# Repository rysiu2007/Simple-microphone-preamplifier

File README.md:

# Dual-Channel Microphone Preamplifier (F4558)

This repository contains the design and documentation for a high-gain microphone preamplifier utilizing the **F4558 Dual Operational Amplifier**. The circuit is optimized for low-noise amplification of small-signal audio inputs.

## ⚡ Circuit Features
*   **Topology:** Inverting Transimpedance Amplifier (TIA) configuration.
*   **Constant Gain:** Fixed by a **470kΩ** precision feedback resistor.
*   **Stability:** Includes a **10pF** compensation capacitor ($C_6/C_7$) in parallel with the feedback loop to prevent high-frequency oscillation and roll off ultrasonic noise.
*   **Biasing:** Virtual ground established at **+6V** (half-supply) to allow for single-supply operation from a +12V source.
*   **Input Stage:** AC-coupled via **4.7µF** electrolytic capacitors with 10kΩ pull-ups for microphone biasing.

## 🖼 Schematic Overview
The design uses both halves of the F4558 (U1A and U1B) to provide dual-channel processing. 

## 📂 Project Files
*   **[mic-amp-report.pdf](mic-amp-report.pdf)**: Full engineering report, including frequency response curves and BOM.
*   **index.html**: Project landing page.

## 🚀 Calculations
The gain for this specific inverting setup is defined by the input impedance of the microphone vs the feedback resistor ($R_f$):

$$V_{out} \approx -I_{in} \times R_f$$

The low-pass cutoff frequency ($f_c$) created by the feedback network is:
$$f_c = \frac{1}{2\pi \times 470k\Omega \times 10pF} \approx 33.8 \text{ kHz}$$
This ensures the full audible spectrum is captured while filtering out unwanted RF interference.

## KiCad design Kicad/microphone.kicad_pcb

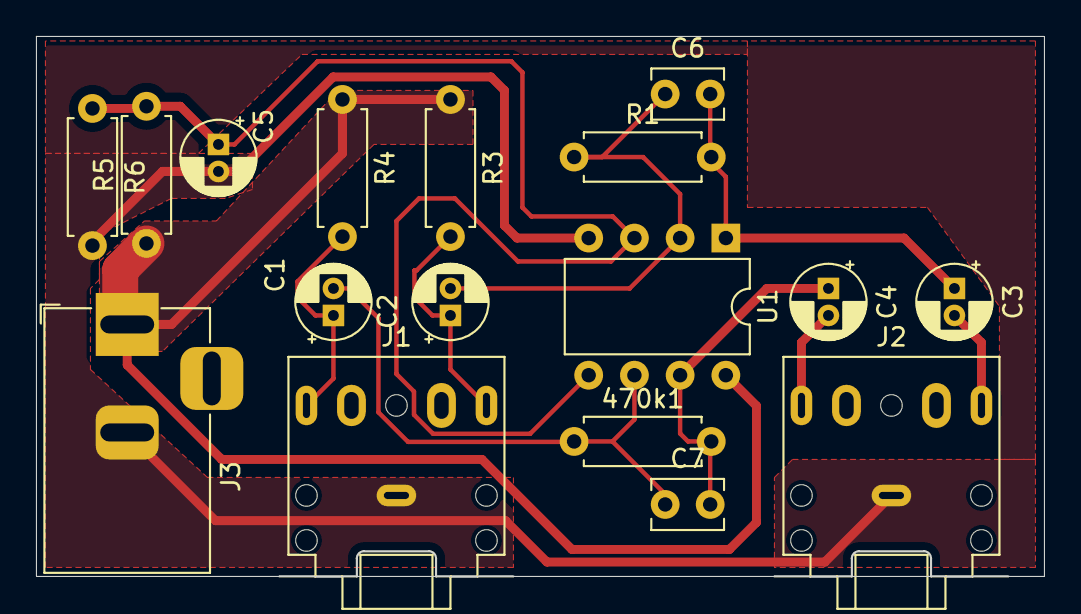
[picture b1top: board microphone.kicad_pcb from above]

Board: 2 copper layers, 56.0 x 30.0 mm, 17 parts (0 on the bottom side), 11 nets.

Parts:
470k1: R; R_Axial_DIN0207_L6.3mm_D2.5mm_P7.62mm_Horizontal
C1, C2, C3, C4, C5: 4.7u; CP_Radial_D4.0mm_P1.50mm
C6, C7: 10p; C_Disc_D3.8mm_W2.6mm_P2.50mm
J1: IN; Jack_3.5mm_CUI_SJ1-3525N_Horizontal
J2: OUT; Jack_3.5mm_CUI_SJ1-3525N_Horizontal
J3: Barrel_Jack_MountingPin; BarrelJack_Horizontal
R1: 470k; R_Axial_DIN0207_L6.3mm_D2.5mm_P7.62mm_Horizontal
R3, R4, R5, R6: 10k; R_Axial_DIN0207_L6.3mm_D2.5mm_P7.62mm_Horizontal
U1: Opamp_Dual; DIP-8_W7.62mm

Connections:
+6V: C5.1, R5.2, R6.1, U1.3 (+), U1.5 (+)
+12V: J3.1, R3.1, R4.1, R5.1, U1.8 (V+)
GNDPWR: C5.2, J1.G, J2.S, J3.2, R6.2, U1.4 (V-)
unnamed: 470k1.2, C4.1, C7.2, U1.7
unnamed: C1.1, J1.R1, R4.2
unnamed: C2.1, J1.T, R3.2
unnamed: C3.1, C6.2, R1.2, U1.1
unnamed: C3.2, J2.T
unnamed: C4.2, J2.R1
unnamed: C2.2, C6.1, R1.1, U1.2 (-)
unnamed: 470k1.1, C1.2, C7.1, U1.6 (-)

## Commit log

2026-05-03 Upload
2026-05-03 Revise README for dual-channel microphone preamplifier
    Expanded the README to include detailed project information, circuit features, schematic overview, project files, and calculations for the microphone preamplifier.
2026-05-03 Change schematic image and update related note
    Updated schematic image reference and note in README.
